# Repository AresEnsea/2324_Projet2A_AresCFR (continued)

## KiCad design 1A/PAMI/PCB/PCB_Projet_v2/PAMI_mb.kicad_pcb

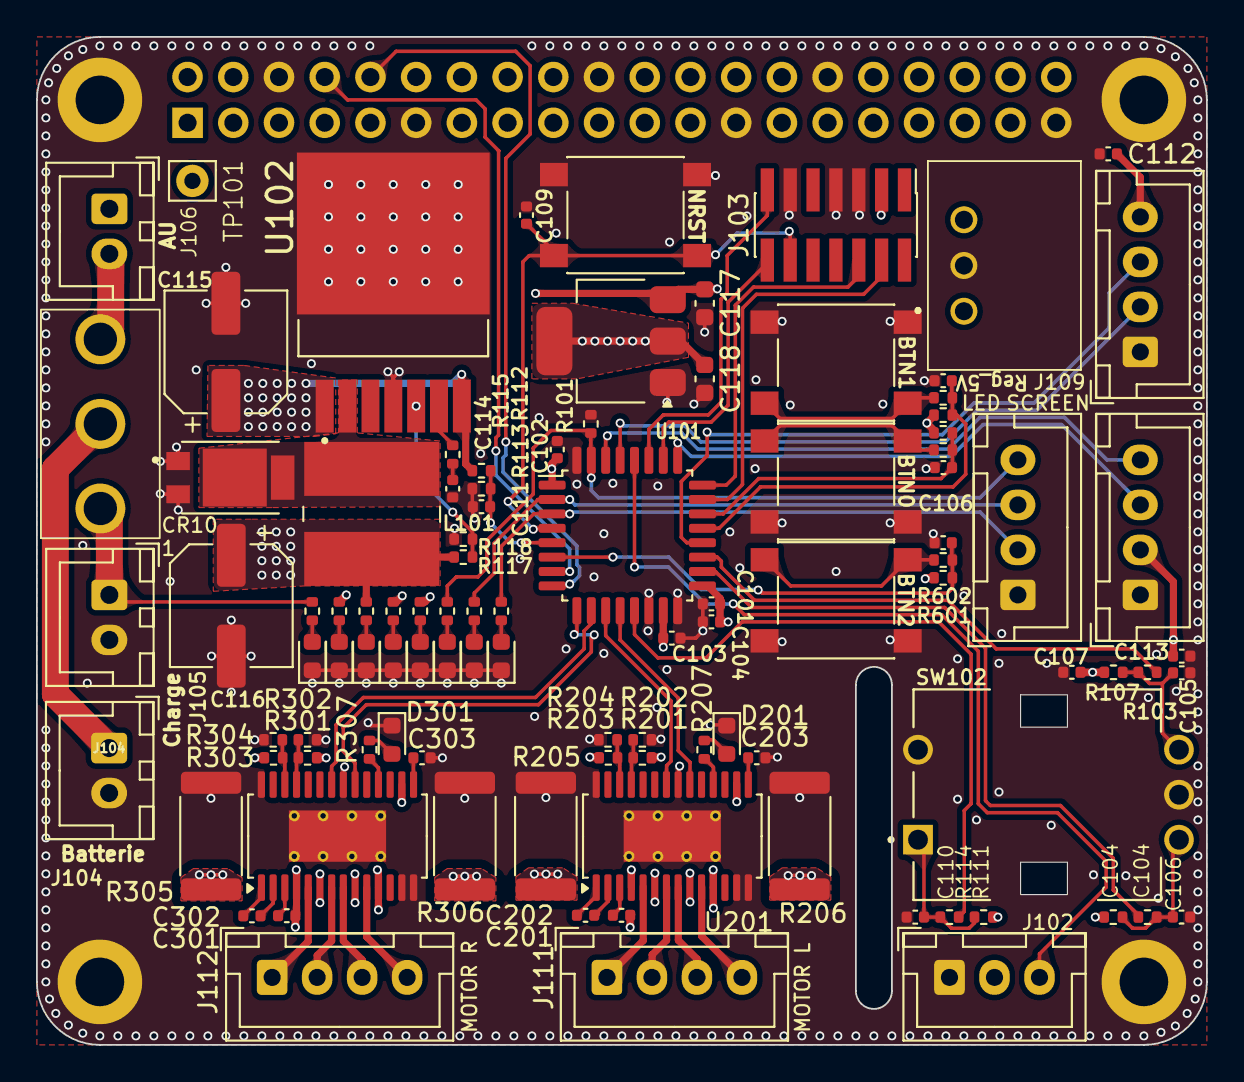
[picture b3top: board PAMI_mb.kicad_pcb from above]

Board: 4 copper layers, 65.0 x 56.0 mm, 106 parts (1 on the bottom side), 80 nets.

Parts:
C101, C102, C103, C107, C111, C201, C301: 100n; C_0402_1005Metric
C104: 10u; C_0402_1005Metric
C105, C106, C109, C110, C114, C401, C501, C601: 10n; C_0402_1005Metric
C112, C113: 1u; C_0402_1005Metric
C115: 100u; CP_Elec_6.3x7.7
C116: 47u; CP_Elec_6.3x5.4
C117, C118: 10u; C_0603_1608Metric
C202, C302: 22n; C_0402_1005Metric
C203, C303: 2u2; C_0402_1005Metric
CR101: DST10100S; DIO_MBR1045STR
D101, D105, D106, D107, D108: LED_RED; LED_0603_1608Metric
D102, D103, D104: LED_GREEN; LED_0603_1608Metric
D201, D301: LED; LED_0603_1608Metric
H101, H102, H103, H104: MountingHole_Pad; MountingHole_2.7mm_M2.5_DIN965_Pad
J101: Conn_02x20_Odd_Even; PinSocket_2x20_P2.54mm_Vertical
J102: Conn_01x03; JST_XH_B3B-XH-A_1x03_P2.50mm_Vertical
J103: Conn_ST_STDC14; PinHeader_2x07_P1.27mm_Vertical_SMD
J104: Battery; JST_XH_B2B-XH-A_1x02_P2.50mm_Vertical
J105: Charge; JST_XH_B2B-XH-A_1x02_P2.50mm_Vertical
J106: Stop; JST_XH_B2B-XH-A_1x02_P2.50mm_Vertical
J107, J109, J110, J111, J112: Conn_01x04; JST_XH_B4B-XH-A_1x04_P2.50mm_Vertical
J108: 173010542
L101: 220u; L_Wuerth_WE-PD2-Typ-L
R101: 100k; R_0402_1005Metric
R102: 560; R_0402_1005Metric
R103, R105, R107, R109, R111, R113, R114, R118, R401, R402, R501, R502, R601, R602: 10k; R_0402_1005Metric
R104, R106, R108, R120: 1k6; R_0402_1005Metric
R110: 5k6; R_0402_1005Metric
R112: 15k; R_0402_1005Metric
R115: 2.7k; R_0402_1005Metric
R116, R119: 3k6; R_0402_1005Metric
R117: 13k; R_0402_1005Metric
R201, R202, R203, R204, R301, R302, R303, R304: 0R; R_0402_1005Metric
R205, R206, R305, R306: 150m; R_2512_6332Metric
R207, R307: 1k; R_0402_1005Metric
SW101: SW_Push_SPDT; 472121010111
SW102: RotaryEncoder_Switch; SW_482016514001
SW103, SW401, SW501, SW601: SW_Push; SW_Push_1P1T_NO_6x6mm_H9.5mm
TP101: TestPoint; Pin_D0.9mm_L10.0mm_W2.4mm_FlatFork
U101: STM32G431KBTx; LQFP-32_7x7mm_P0.8mm
U102: LT1076CR-PBF; DPAK127P1394X457-8N
U103: AZ1117CH2-3.3TRG1; SOT-223-3_TabPin2
U201, U301: TMC2225-SA-T; HTSSOP-28-1EP_4.4x9.7mm_P0.65mm_EP2.85x5.4mm_ThermalVias

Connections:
+3.3V: C101.1, C102.1, C103.1, C104.1, C107.2, C113.1, C118.1, J102.2, J103.3 (VCC), J110.2, R107.2, R109.2, R111.1, R120.1, R201.2, R203.2, R301.2, R303.2, R401.1, R501.1, R601.1, U101.1 (VDD), U101.15 (VDDA), U101.17 (VDD), U103.2 (VO), U201.16 (VCC_IO), U301.16 (VCC_IO)
+5.1V: C116.1, J101.2, J101.4, L101.2, R117.1, R119.1
+5V: C112.1, C117.1, J108.3 (VOUT), J109.4, R116.1, U103.3 (VI)
/ADC_BATT: C111.1, R112.2, R113.1, U101.5 (PA0)
/DATA_RECEIVER: J102.3, U101.28 (PB5)
/DIR_MOTOR_L: U101.12 (PA7), U201.20 (DIR)
/DIR_MOTOR_R: U101.9 (PA4), U301.20 (DIR)
/ENCODEUR_A: R105.1, U101.18 (PA8)
/ENCODEUR_B: R103.1, U101.19 (PA9)
/ENCODEUR_BTN: R114.2, U101.13 (PB0)
/I2C_SCL: J110.3, U101.25 (PA15)
/I2C_SDA: J110.4, U101.30 (PB7)
/LIDAR_LP_RX: J109.3, U101.20 (PA10)
/LIDAR_LP_TX: J109.2, U101.29 (PB6)
/NRST: C109.1, J103.12 (~RST), SW103.1, U101.4 (PG10)
/PA1_USR_BTN_0: C401.1, R401.2, R402.1, U101.22 (PA12)
/PA11_USR_BTN_1: C501.1, R501.2, R502.1, U101.21 (PA11)
/PA12_USR_BTN_2: C601.1, R601.2, R602.1, U101.6 (PA1)
/PB8-BOOT0_LED0: J107.4, R101.1, R104.1, U101.31 (PB8)
/PF0_LED1: J107.3, R106.1, U101.2 (PF0)
/PF1_LED2: J107.2, R108.1, U101.3 (PF1)
/PWM_MOTOR_L_TIM2_CH1: U101.11 (PA6), U201.22 (STEP)
/PWM_MOTOR_R_TIM3_CH1: U101.10 (PA5), U301.22 (STEP)
/RASPBERRY_PI_RX: J101.10, U101.8 (PA3)
/RASPBERRY_PI_TX: J101.8, U101.7 (PA2)
/STLINK_RX: J103.13 (VCP_RX), U101.27 (PB4)
/STLINK_TX: J103.14 (VCP_TX), U101.26 (PB3)
/SWCLK: J103.6 (JCLK/SWCLK), U101.24 (PA14)
/SWDIO: J103.4 (JTMS/SWDIO), U101.23 (PA13)
/TMC2225/OA1: J111.2, U201.7 (OA1)
/TMC2225/OA2: J111.1, U201.5 (OA2)
/TMC2225/OB1: J111.3, U201.8 (OB1)
/TMC2225/OB2: J111.4, U201.10 (OB2)
/TMC2226/OA1: J112.2, U301.7 (OA1)
/TMC2226/OA2: J112.1, U301.5 (OA2)
/TMC2226/OB1: J112.3, U301.8 (OB1)
/TMC2226/OB2: J112.4, U301.10 (OB2)
/VFB: R117.2, R118.1, U102.5 (FB)
/V_BAT: J104.1, SW101.2 (B)
/V_CHARGE: J105.1, R102.1, SW101.3 (C)
/Vsw: CR101.3, L101.1, U102.2 (Vsw)
GND: C101.2, C102.2, C103.2, C104.2, C105.2, C106.2, C107.1, C109.2, C110.2, C111.2, C112.2, C113.2, C114.2, C115.2, C116.2, C117.2, C118.2, C203.1, C303.1, C401.2, C501.2, C601.2, CR101.1, CR101.2, D101.1 (K), D102.1 (K), D103.1 (K), D104.1 (K), D105.1 (K), D106.1 (K), D107.1 (K), D108.1 (K), D201.1 (K), D301.1 (K), H101.1, H102.1, H103.1, H104.1, J101.6, J101.11, J101.20, J101.25, J101.30, J101.39, J102.1, J103.5 (GND), J103.7 (GND), J103.11 (GNDDetect), J104.2, J105.2, J107.1, J108.2 (GND), J109.1, J110.1, R101.2, R113.2, R118.2, R202.1, R204.1, R205.2, R206.2, R302.1, R304.1, R305.2, R306.2, SW102.C, SW102.S2, SW103.2, SW401.2, SW501.2, SW601.2, U101.14 (VSSA), U101.16 (VSS), U101.32 (VSS), U102.4 (GND), U103.1 (GND), U201.13 (TEST), U201.14 (GND), U201.21 (ENN), U201.28 (GND), U201.29 (PAD), U301.13 (TEST), U301.14 (GND), U301.21 (ENN), U301.28 (GND), U301.29 (PAD)
unnamed: C105.1, R103.2, R107.1, SW102.B
unnamed: C106.1, R105.2, R109.1, SW102.A
unnamed: C110.1, R111.2, R114.1, SW102.S1
unnamed: C114.1, R115.2
unnamed: D101.2 (A), R102.2
unnamed: D102.2 (A), R104.2
unnamed: D103.2 (A), R106.2
unnamed: D104.2 (A), R108.2
unnamed: D105.2 (A), R110.2
unnamed: D106.2 (A), R116.2
unnamed: D107.2 (A), R119.2
unnamed: D108.2 (A), R120.2
unnamed: D201.2 (A), R207.1
unnamed: D301.2 (A), R307.1
unnamed: J106.2, SW101.1 (A)
unnamed: R402.2, SW401.1
unnamed: R502.2, SW501.1
unnamed: R602.2, SW601.1
unnamed: R115.1, U102.6 (Vc)
unnamed: C203.2, U201.15 (5VOUT)
unnamed: R205.1, U201.6 (BRA)
unnamed: R206.1, U201.9 (BRB)
unnamed: C202.1, U201.2 (CPI)
unnamed: C202.2, U201.1 (CPO)
unnamed: R207.2, U201.18 (DIAG)
unnamed: R201.1, R202.2, U201.25 (MS1)
unnamed: R203.1, R204.2, U201.26 (MS2)
unnamed: C201.2, U201.3 (VCP)
unnamed: C303.2, U301.15 (5VOUT)
unnamed: R305.1, U301.6 (BRA)
unnamed: R306.1, U301.9 (BRB)
unnamed: C302.1, U301.2 (CPI)
unnamed: C302.2, U301.1 (CPO)
unnamed: R307.2, U301.18 (DIAG)
unnamed: R301.1, R302.2, U301.25 (MS1)
unnamed: R303.1, R304.2, U301.26 (MS2)
unnamed: C301.2, U301.3 (VCP)
VCC: C115.1, C201.1, C301.1, J106.1, J108.1 (VIN), R110.1, R112.1, TP101.1, U102.1 (Vin), U102.7 (Shutdown), U201.4 (VS), U201.11 (VS), U301.4 (VS), U301.11 (VS)

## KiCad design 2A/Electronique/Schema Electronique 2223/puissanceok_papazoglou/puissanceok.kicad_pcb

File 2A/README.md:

# 2A
Ce dossier regroupe les fichiers réalisés par les étudiants en deuxième année de l'association

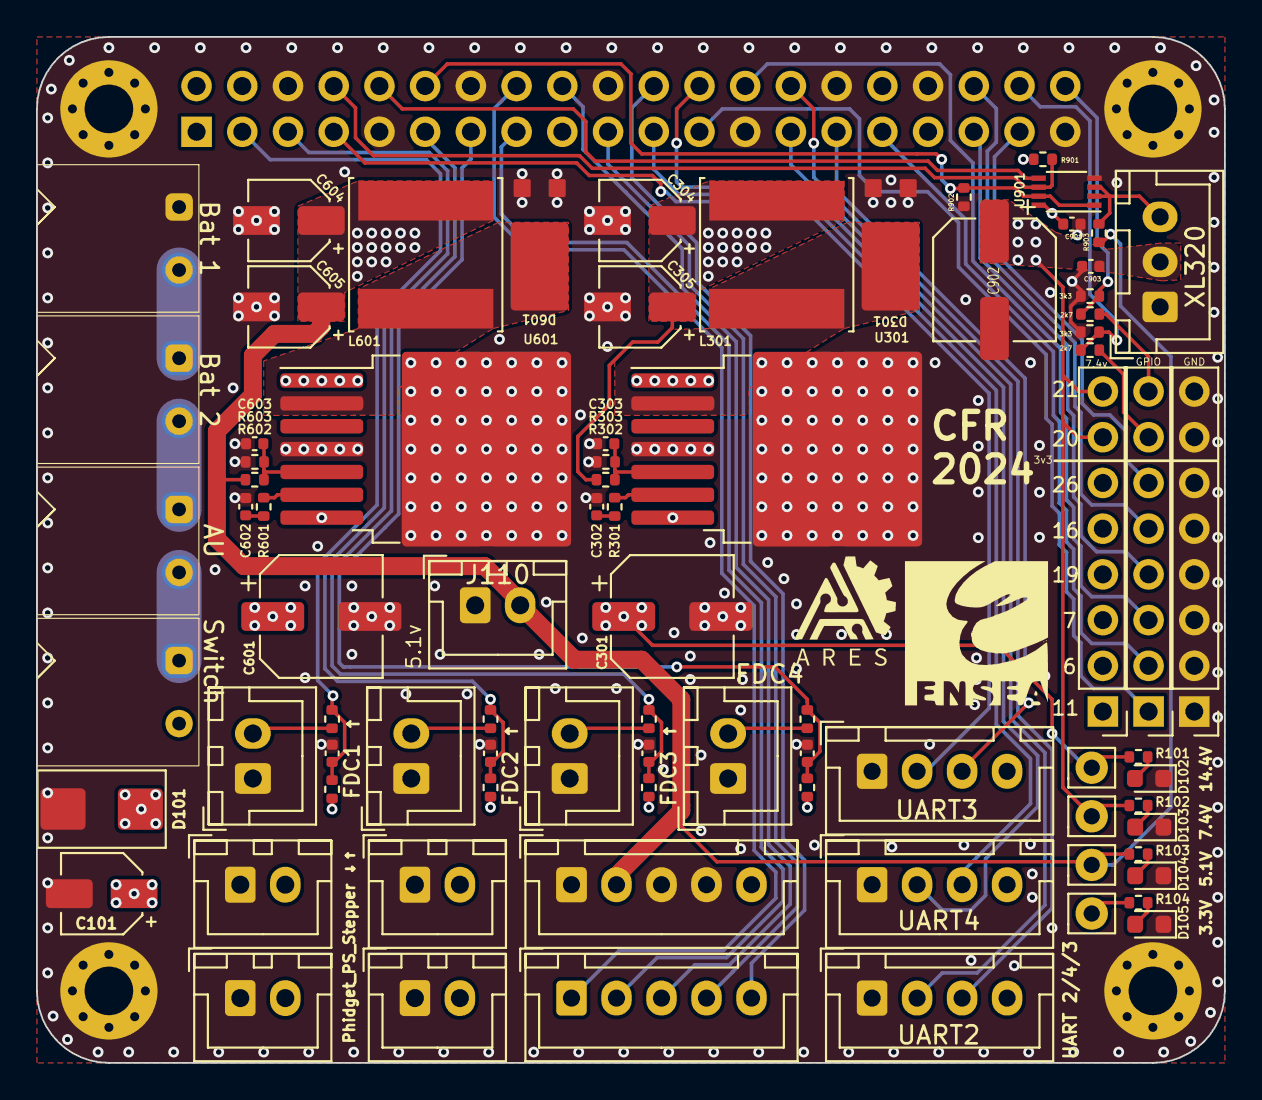
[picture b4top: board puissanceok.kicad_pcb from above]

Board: 4 copper layers, 66.0 x 57.0 mm, 86 parts (1 on the bottom side), 53 nets.

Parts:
C101: 10u; CP_Elec_4x5.4
C201, C401, C501, C701, C901, C903: 100n; C_0402_1005Metric
C301, C601, C902: 100u; CP_Elec_6.3x7.7
C302, C303, C602, C603: 10n; C_0402_1005Metric
C304, C305, C604, C605: 22u; CP_Elec_4x5.4
D101: TVS 20.5V; D_SMB
D102, D103, D104, D105: LED; LED_0603_1608Metric
D301, D601: D_Schottky; DST10100S
H101, H102, H103, H104: MountingHole_Pad; MountingHole_2.7mm_M2.5_Pad_Via
J101: Bat 2; 691322110002
J102: Bat 1; 691322110002
J103: AU; 691322110002
J104: Switch; 691322110002
J105: Conn_RPI; PinSocket_2x20_P2.54mm_Vertical
J106: Conn_Phidget_PS_Stepper_1; JST_XH_B2B-XH-A_1x02_P2.50mm_Vertical
J107: Conn_Phidget_PS_Stepper_2; JST_XH_B2B-XH-A_1x02_P2.50mm_Vertical
J108: Conn_Phidget_PS_Stepper_3; JST_XH_B2B-XH-A_1x02_P2.50mm_Vertical
J109: Conn_Phidget_PS_Stepper_4; JST_XH_B2B-XH-A_1x02_P2.50mm_Vertical
J110: Conn_01x02; JST_XH_B2B-XH-A_1x02_P2.50mm_Vertical
J111: Conn_GND; PinHeader_1x08_P2.54mm_Vertical
J112: Conn_GPIO_unused; PinHeader_1x08_P2.54mm_Vertical
J113: Conn_3.3V; PinHeader_1x08_P2.54mm_Vertical
J114, J115: Conn_01x05; JST_XH_B5B-XH-A_1x05_P2.50mm_Vertical
J201, J401, J501, J701: Conn_FDC; JST_XH_B2B-XH-A_1x02_P2.50mm_Vertical
J801, J1001, J1101: Conn_UART; JST_XH_B4B-XH-A_1x04_P2.50mm_Vertical
J901: Conn_XL320; JST_XH_B3B-XH-A_1x03_P2.50mm_Vertical
L301, L601: 22m; L_Changjiang_FNR8065S
R1, R3: 2k7; R_0402_1005Metric
R2, R4: 3k3; R_0402_1005Metric
R101: 4k7; R_0402_1005Metric
R102: 1k8; R_0402_1005Metric
R103, R104, R202, R402, R502, R702: 1k; R_0402_1005Metric
R201, R401, R501, R701: 100k; R_0402_1005Metric
R301, R601: 2.7k; R_0402_1005Metric
R302, R602: 2k87; R_0402_1005Metric
R303, R603: 2k2; R_0402_1005Metric
R901, R902, R903: 10k; R_0402_1005Metric
TP101: TestPoint; Pin_D0.9mm_L10.0mm_W2.4mm_FlatFork
TP102: 5.1V; Pin_D0.9mm_L10.0mm_W2.4mm_FlatFork
TP103: 7.4V; Pin_D0.9mm_L10.0mm_W2.4mm_FlatFork
TP104: 3V3; Pin_D0.9mm_L10.0mm_W2.4mm_FlatFork
U301, U601: LT1076CR-PBF; TO-263-7_TabPin4
U901: 74LVC2G241; VSSOP-8_2.3x2mm_P0.5mm

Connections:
5.1V: C604.1, C605.1, J105.2, J105.4, J110.2, J114.2, L601.2, R103.1, R602.1, R903.1, TP102.1
7.4V: C304.1, C305.1, C902.1, C903.1, J113.7, J113.8, J901.2, L301.2, R102.1, R302.1, TP103.1
14.4V: C101.1, C301.1, C601.1, D101.1 (A1), J104.2, J106.2, J107.2, J108.2, J109.2, R101.1, TP101.1, U301.1 (Vin), U301.7 (Shutdown), U601.1 (Vin), U601.7 (Shutdown)
+3.3V: C901.1, J105.17, J113.1, J113.2, J113.3, J113.4, J113.5, J113.6, J114.5, J801.4, J1001.4, J1101.4, R104.1, R201.1, R401.1, R501.1, R701.1, R901.1, TP104.1, U901.8 (VCC)
/BUCK_5.1V/vc: R601.1, U601.6 (Vc)
/BUCK_5.1V/voutbuck: D601.1 (K), L601.1, U601.2 (Vsw)
/BUCK_7.4V/vc: R301.1, U301.6 (Vc)
/BUCK_7.4V/voutbuck: D301.1 (K), L301.1, U301.2 (Vsw)
/FDC_1: C201.1, J105.3, R201.2, R202.1
/FDC_2: C401.1, J105.5, R401.2, R402.1
/FDC_3: C501.1, J105.11, R501.2, R502.1
/FDC_4: C701.1, J105.13, R701.2, R702.1
/GPIO6: J105.31, J112.2
/GPIO7: J105.26, J112.3
/GPIO11: J105.23, J112.1
/GPIO16: J105.36, J112.5
/GPIO19: J105.35, J112.4
/GPIO20: J105.38, R3.2, R4.1
/GPIO21: J105.40, R1.2, R2.1
/GPIO26: J105.37, J112.6
/Out_color_sensor: J105.16, J115.1
/S0_color_sensor: J105.22, J115.5
/S1_color_sensor: J105.19, J115.4
/S2_color_sensor: J105.18, J115.3
/S3_color_sensor: J105.15, J115.2
/Uart1_RX: J105.10, U901.5
/Uart1_TX: J105.8, R901.2, U901.6
/Uart2_RX: J105.28, J801.3
/Uart2_TX: J105.27, J801.2
/Uart3_RX: J105.29, J1001.3
/Uart3_TX: J105.7, J1001.2
/Uart4_RX: J105.21, J1101.3
/Uart4_TX: J105.24, J1101.2
/UartTX_Enable: J105.12, R902.1, U901.1, U901.7
/V_BAT: J101.2, J103.1
/XL_320_connector_and_buffer/DXL_Data: J901.3, R903.2, U901.2, U901.3
GND: C101.2, C201.2, C301.2, C302.2, C303.2, C304.2, C305.2, C401.2, C501.2, C601.2, C602.2, C603.2, C604.2, C605.2, C701.2, C901.2, C902.2, C903.2, D101.2 (A2), D102.1 (K), D103.1 (K), D104.1 (K), D105.1 (K), D301.2 (A), D601.2 (A), H101.1, H102.1, H103.1, H104.1, J102.1, J105.6, J105.9, J105.14, J105.20, J105.25, J105.30, J105.34, J105.39, J106.1, J107.1, J108.1, J109.1, J110.1, J111.1, J111.2, J111.3, J111.4, J111.5, J111.6, J111.7, J111.8, J114.1, J114.3, J114.4, J201.1, J401.1, J501.1, J701.1, J801.1, J901.1, J1001.1, J1101.1, R2.2, R4.2, R303.2, R603.2, R902.2, U301.4 (GND), U601.4 (GND), U901.4 (GND)
unnamed: C302.1, R301.2
unnamed: C602.1, R601.2
unnamed: D102.2 (A), R101.2
unnamed: D103.2 (A), R102.2
unnamed: D104.2 (A), R103.2
unnamed: D105.2 (A), R104.2
unnamed: J101.1, J102.2
unnamed: J103.2, J104.1
unnamed: J112.7, R3.1
unnamed: J112.8, R1.1
unnamed: J201.2, R202.2
unnamed: J401.2, R402.2
unnamed: J501.2, R502.2
unnamed: J701.2, R702.2
unnamed: C303.1, R302.2, R303.1, U301.5 (FB)
unnamed: C603.1, R602.2, R603.1, U601.5 (FB)

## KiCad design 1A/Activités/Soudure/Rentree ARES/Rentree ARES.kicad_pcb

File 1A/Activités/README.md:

# Activités
Ce dossier regroupe deux livrets rédigés par Ousmane THIONGANE. L'un permet de découvrir la programmation avec Mbed, et l'autre le routage avec KiCad. Il peuvent être réutilisés au fil des années pour réaliser des activités de rentrée, ou simplement pour s'exercer à l'électronique et l'informatique.

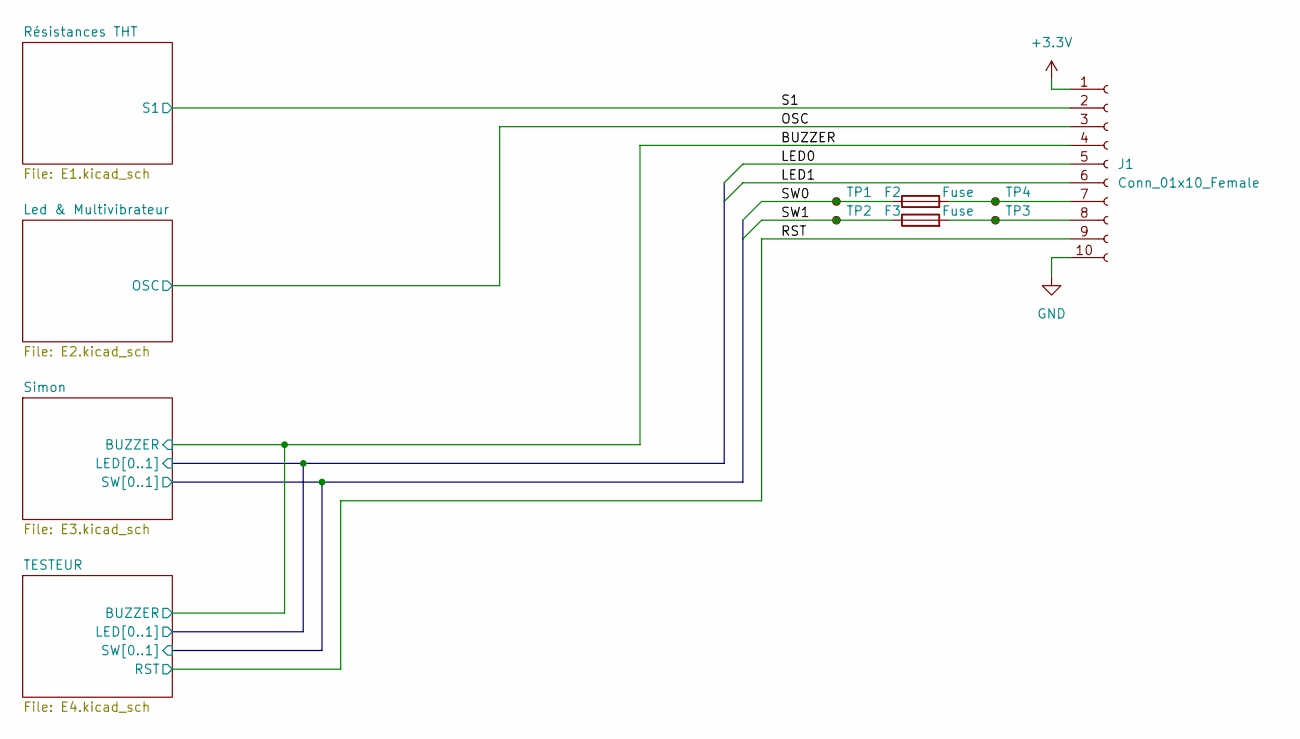
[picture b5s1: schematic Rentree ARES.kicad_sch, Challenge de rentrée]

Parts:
F2, F3: Fuse; Fuse_internal_trace
J1: Conn_01x10_Female; PinHeader_1x10_P2.54mm_Horizontal
TP1, TP2, TP3, TP4: TestPoint_Small; TestPoint_Pad_D1.5mm

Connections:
+3.3V: J1.1; also elsewhere on the board
/BUZZER: J1.4; also elsewhere on the board
/OSC: J1.3; also elsewhere on the board
/RST: J1.9; also elsewhere on the board
/S1: J1.2; also elsewhere on the board
/Simon un peu plus dur/LED0: J1.5; also elsewhere on the board
/Simon un peu plus dur/LED1: J1.6; also elsewhere on the board
/Simon un peu plus dur/SW0: F2.1, TP1.1; also elsewhere on the board
/Simon un peu plus dur/SW1: F3.1, TP2.1; also elsewhere on the board
GND: J1.10; also elsewhere on the board
unnamed: F2.2, J1.7, TP4.1
unnamed: F3.2, J1.8, TP3.1

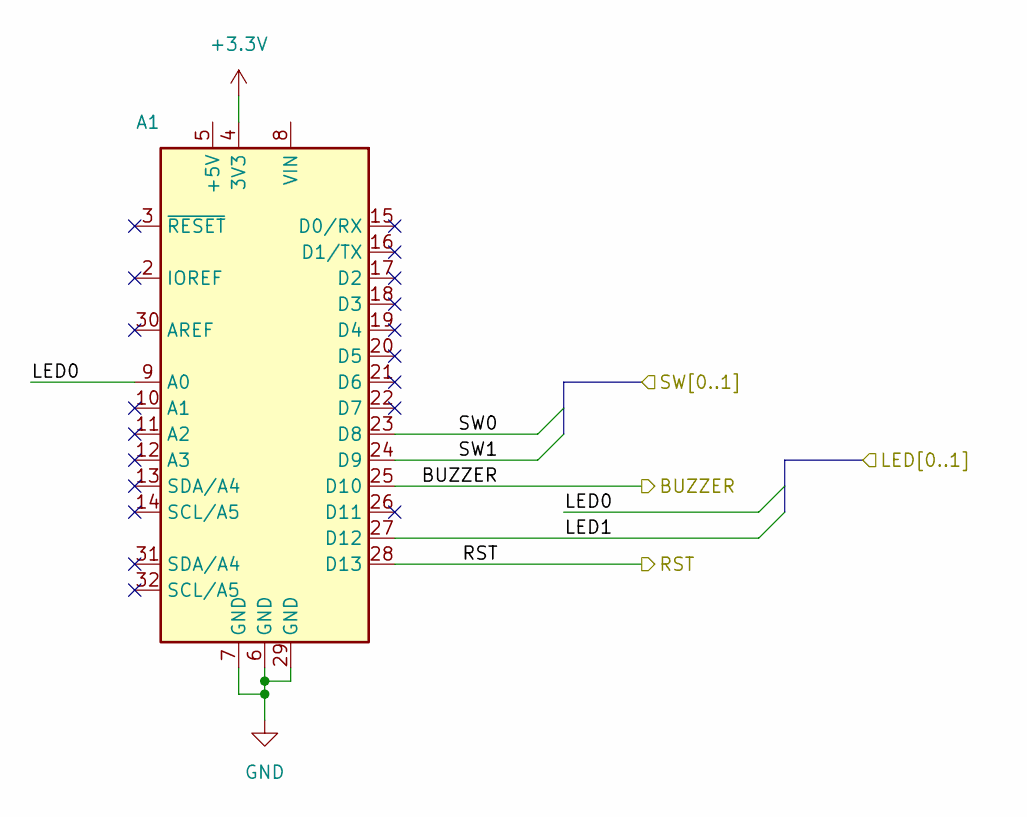
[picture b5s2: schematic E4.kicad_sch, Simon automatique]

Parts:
A1: Arduino_UNO_R3

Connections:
+3.3V: A1.4 (3V3); also elsewhere on the board
/BUZZER: A1.25 (D10); also elsewhere on the board
/RST: A1.28 (D13); also elsewhere on the board
/Simon un peu plus dur/LED0: A1.9 (A0); also elsewhere on the board
/Simon un peu plus dur/LED1: A1.27 (D12); also elsewhere on the board
/Simon un peu plus dur/SW0: A1.23 (D8); also elsewhere on the board
/Simon un peu plus dur/SW1: A1.24 (D9); also elsewhere on the board
GND: A1.6 (GND), A1.7 (GND), A1.29 (GND); also elsewhere on the board

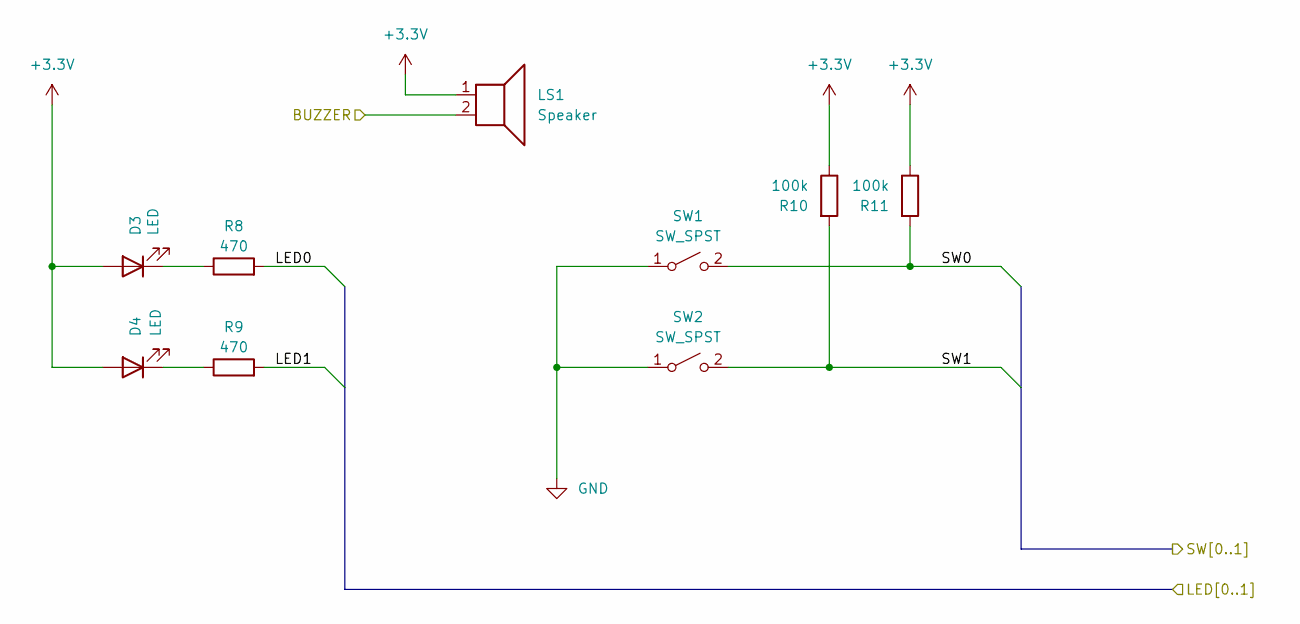
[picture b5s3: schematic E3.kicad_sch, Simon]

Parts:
D3, D4: LED; LED_D5.0mm_Clear
LS1: Speaker; MagneticBuzzer_ProSignal_ABT-410-RC
R8, R9: 470; R_0805_2012Metric
R10, R11: 100k; R_0805_2012Metric
SW1, SW2: SW_SPST; SW_PUSH_6mm_H5mm

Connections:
+3.3V: D3.2 (A), D4.2 (A), LS1.1, R10.1, R11.1; also elsewhere on the board
/BUZZER: LS1.2; also elsewhere on the board
/Simon un peu plus dur/LED0: R8.2; also elsewhere on the board
/Simon un peu plus dur/LED1: R9.2; also elsewhere on the board
/Simon un peu plus dur/SW0: R11.2, SW1.2 (B); also elsewhere on the board
/Simon un peu plus dur/SW1: R10.2, SW2.2 (B); also elsewhere on the board
GND: SW1.1 (A), SW2.1 (A); also elsewhere on the board
unnamed: D3.1 (K), R8.1
unnamed: D4.1 (K), R9.1

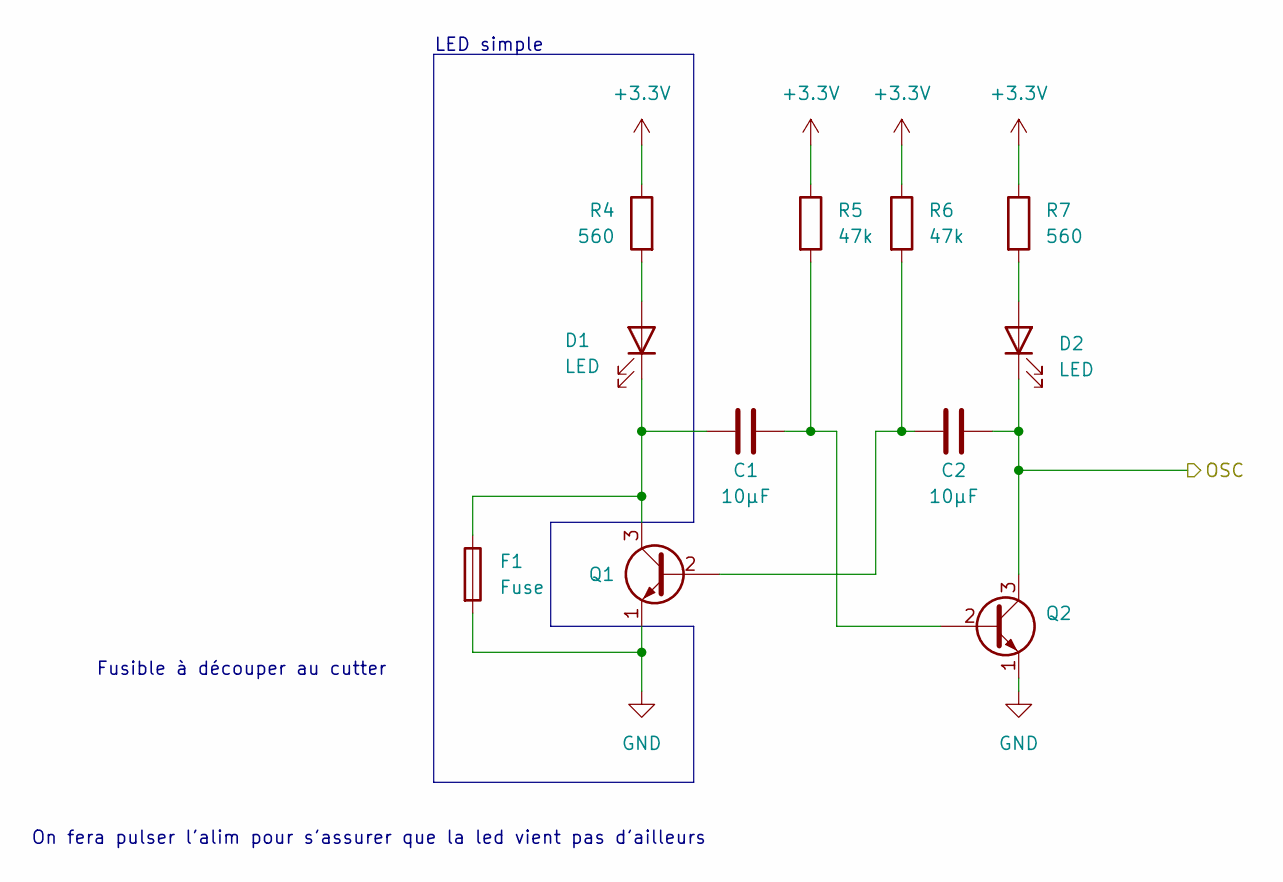
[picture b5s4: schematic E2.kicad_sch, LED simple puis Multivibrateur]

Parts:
C1, C2: 10µF; C_1206_3216Metric
D1, D2: LED; LED_D5.0mm_Clear
F1: Fuse; Fuse_trace
Q1, Q2: Q_NPN_EBC; TO-92_Inline
R4, R7: 560; R_0805_2012Metric
R5, R6: 47k; R_0805_2012Metric

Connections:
+3.3V: R4.1, R5.1, R6.1, R7.1; also elsewhere on the board
/OSC: C2.1, D2.1 (K), Q2.3 (C); also elsewhere on the board
GND: F1.2, Q1.1 (E), Q2.1 (E); also elsewhere on the board
unnamed: C1.1, Q2.2 (B), R5.2
unnamed: C1.2, D1.1 (K), F1.1, Q1.3 (C)
unnamed: C2.2, Q1.2 (B), R6.2
unnamed: D1.2 (A), R4.2
unnamed: D2.2 (A), R7.2

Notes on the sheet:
LED simple
Fusible à découper au cutter
On fera pulser l'alim pour s'assurer que la led vient pas d'ailleurs

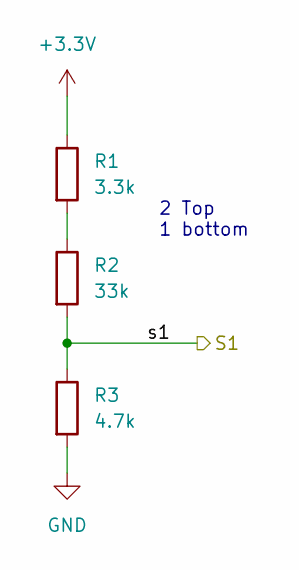
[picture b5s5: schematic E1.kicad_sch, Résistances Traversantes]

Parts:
R1: 3.3k; R_Axial_DIN0207_L6.3mm_D2.5mm_P2.54mm_Vertical
R2: 33k; R_Axial_DIN0207_L6.3mm_D2.5mm_P10.16mm_Horizontal
R3: 4.7k; R_Axial_DIN0207_L6.3mm_D2.5mm_P10.16mm_Horizontal

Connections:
+3.3V: R1.1; also elsewhere on the board
/S1: R2.2, R3.1; also elsewhere on the board
GND: R3.2; also elsewhere on the board
unnamed: R1.2, R2.1

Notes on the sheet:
2 Top 1 bottom

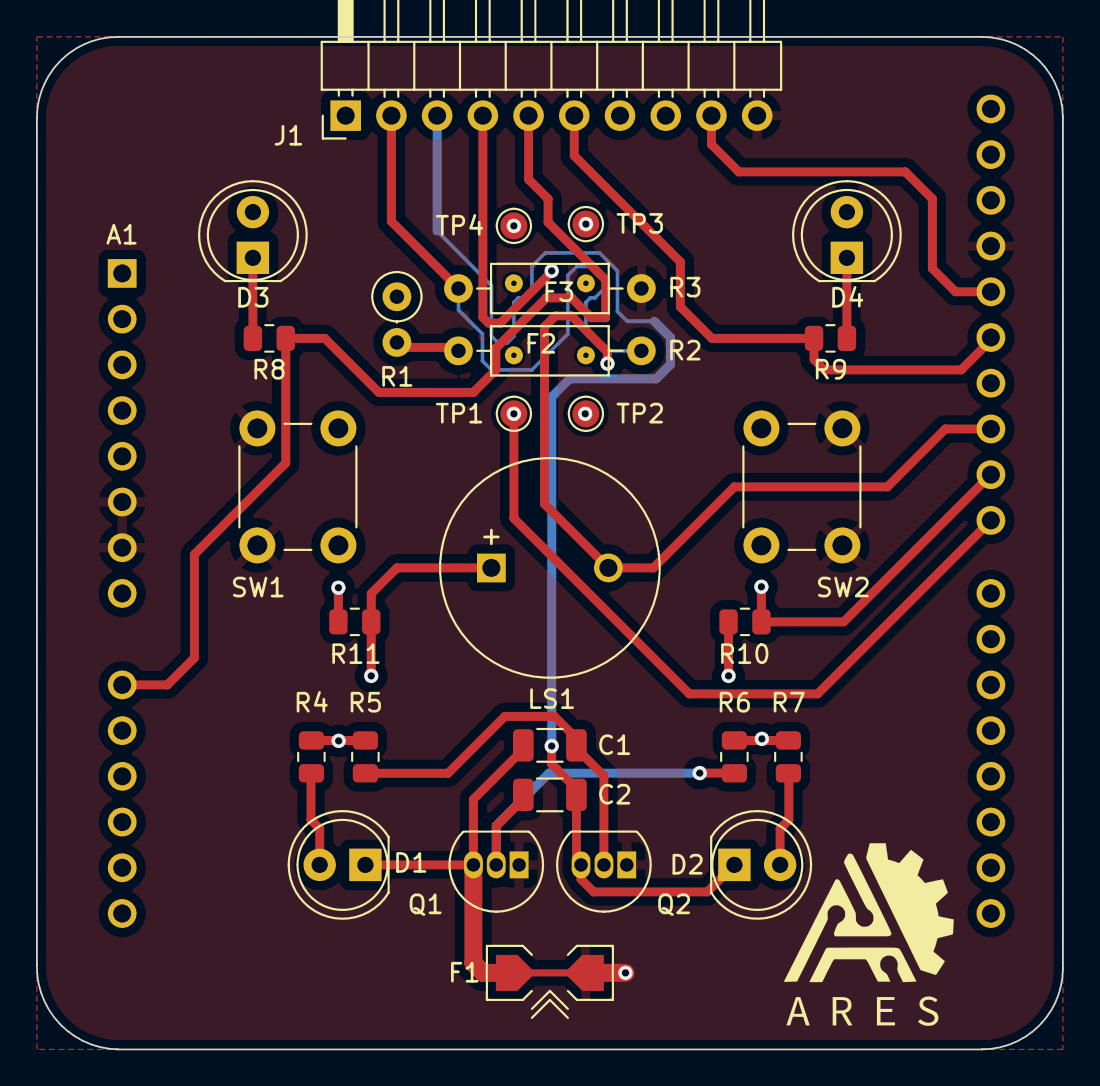
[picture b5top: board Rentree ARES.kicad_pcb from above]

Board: 4 copper layers, 57.0 x 56.2 mm, 31 parts (0 on the bottom side), 20 nets.

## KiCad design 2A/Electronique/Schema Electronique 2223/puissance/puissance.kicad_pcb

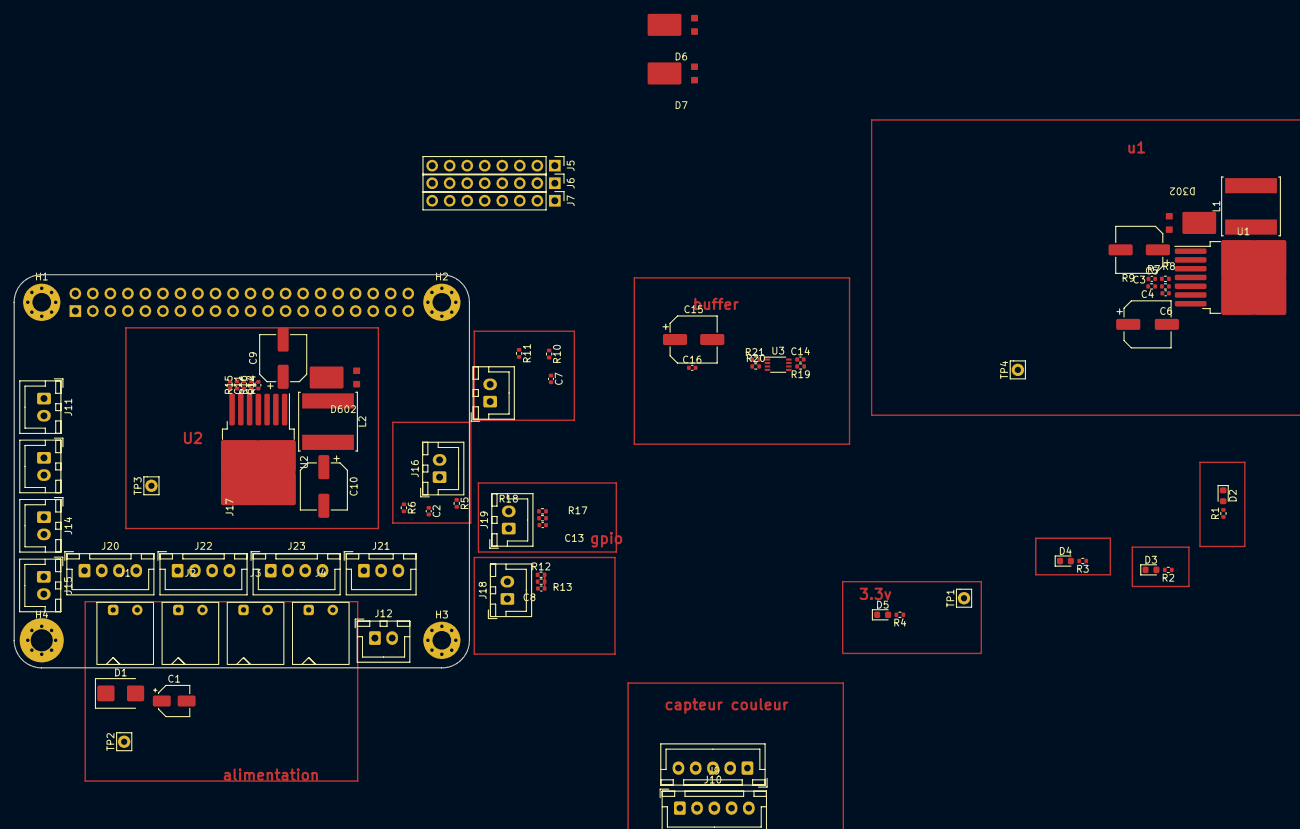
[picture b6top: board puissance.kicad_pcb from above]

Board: 2 copper layers, 82 parts (1 on the bottom side), 34 nets.

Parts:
C1: 10u; CP_Elec_4x5.4
C2, C5, C14, C16: 100n; C_0402_1005Metric
C3: 100n; CP_Elec_6.3x7.7
C4: 100n; CP_Elec_6.3x5.4
C6: 100u; C_0402_1005Metric
C7, C8, C11, C12: 10n; C_0402_1005Metric
C9: 47u; CP_Elec_6.3x7.7
C10: 100u; CP_Elec_6.3x5.4
C13: 47u; C_0402_1005Metric
C15: 100u; CP_Elec_6.3x7.7
D1: TVS 20.5V; D_SMB
D2, D3, D4, D5: LED; LED_0603_1608Metric
D6, D7, D302, D602: D_Schottky; DST10100S
H1, H2, H3, H4: MountingHole_Pad; MountingHole_2.7mm_M2.5_Pad_Via
J1: Bat 2; 691322110002
J2: Bat 1; 691322110002
J3: AU; 691322110002
J4: Switch; 691322110002
J5: Conn_RPI; PinHeader_1x08_P2.54mm_Vertical
J6: Conn_Phidget_PS_Stepper_1; PinHeader_1x08_P2.54mm_Vertical
J7: Conn_Phidget_PS_Stepper_2; PinHeader_1x08_P2.54mm_Vertical
J8: Conn_Phidget_PS_Stepper_3; PinSocket_2x20_P2.54mm_Vertical
J9: Conn_Phidget_PS_Stepper_4; JST_XH_B5B-XH-A_1x05_P2.50mm_Vertical
J10: Conn_01x02; JST_XH_B5B-XH-A_1x05_P2.50mm_Vertical
J11: Conn_GND; JST_XH_B2B-XH-A_1x02_P2.50mm_Vertical
J12: Conn_GPIO_unused; JST_XH_B2B-XH-A_1x02_P2.50mm_Vertical
J13: Conn_3.3V; JST_XH_B2B-XH-A_1x02_P2.50mm_Vertical
J14, J15: Conn_01x05; JST_XH_B2B-XH-A_1x02_P2.50mm_Vertical
J16, J17, J18, J19: Conn_FDC; JST_XH_B2B-XH-A_1x02_P2.50mm_Vertical
J20, J23: Conn_UART; JST_XH_B4B-XH-A_1x04_P2.50mm_Vertical
J21: Conn_UART; JST_XH_B3B-XH-A_1x03_P2.50mm_Vertical
J22: Conn_XL320; JST_XH_B4B-XH-A_1x04_P2.50mm_Vertical
L1, L2: 22m; L_Changjiang_FNR8065S
R1: 4k7; R_0402_1005Metric
R2: 1k8; R_0402_1005Metric
R3, R4, R6, R8, R10, R12: 1k; R_0402_1005Metric
R5, R7, R9, R11: 100k; R_0402_1005Metric
R13, R16: 2.7k; R_0402_1005Metric
R14, R17: 2k87; R_0402_1005Metric
R15, R18: 2k2; R_0402_1005Metric
R19, R20, R21: 10k; R_0402_1005Metric
TP1: TestPoint; Pin_D0.9mm_L10.0mm_W2.4mm_FlatFork
TP2: 5.1V; Pin_D0.9mm_L10.0mm_W2.4mm_FlatFork
TP3: 7.4V; Pin_D0.9mm_L10.0mm_W2.4mm_FlatFork
TP4: 3V3; Pin_D0.9mm_L10.0mm_W2.4mm_FlatFork
U1, U2: LT1076CR-PBF; TO-263-7_TabPin4
U3: 74LVC2G241; VSSOP-8_2.3x2mm_P0.5mm

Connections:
5.1V: C13.1, J5.2, J5.4, J10.2, L2.2, R3.1, R17.1, R21.1, TP2.1
7.4V: C9.1, C15.1, C16.1, J22.2, L1.2, R2.1, R14.1, TP3.1
+3.3V: C14.1, J5.1, J13.1, J13.2, J20.4, J23.4, R4.1, R5.1, R7.1, R9.1, R11.1, R19.1, TP4.1, U3.8 (VCC)
/FDC_1: C4.1, R9.2, R10.1
/FDC_2: C3.1, R7.2, R8.1
/FDC_3: C5.1, R11.2, R12.1
/FDC_4: C2.1, R5.2, R6.1
/GPIO2: J5.3, J12.1
/GPIO3: J5.5, J12.2
/Uart1_TX: J5.8, R19.2, U3.6
/Uart3_TX: J5.7, J21.2
/UartTX_Enable: R20.1, U3.1, U3.7
/V_BAT: J1.2, J3.1
/XL_320_connector_and_buffer/DXL_Data: J22.3, R21.2, U3.2, U3.3
GND: C1.2, C2.2, C3.2, C4.2, C5.2, C6.2, C7.2, C8.2, C9.2, C10.2, C11.2, C12.2, C13.2, C14.2, C15.2, C16.2, D1.2 (A2), D2.1 (K), D3.1 (K), D4.1 (K), D5.1 (K), D6.2 (A), D7.2 (A), H1.1, H2.1, H3.1, H4.1, J2.1, J5.6, J6.1, J7.1, J8.1, J9.1, J10.1, J11.1, J11.2, J14.2, J16.1, J17.1, J18.1, J19.1, J20.1, J21.1, J22.1, J23.1, R15.2, R18.2, R20.2, U1.4 (GND), U2.4 (GND), U3.4 (GND)
unnamed: C7.1, R13.2
unnamed: C11.1, R16.2
unnamed: D2.2 (A), R1.2
unnamed: D3.2 (A), R2.2
unnamed: D4.2 (A), R3.2
unnamed: D5.2 (A), R4.2
unnamed: D6.1 (K), L1.1, U1.2 (Vsw)
unnamed: D7.1 (K), L2.1, U2.2 (Vsw)
unnamed: J1.1, J2.2
unnamed: J3.2, J4.1
unnamed: J16.2, R6.2
unnamed: J17.2, R8.2
unnamed: J18.2, R10.2
unnamed: J19.2, R12.2
unnamed: C8.1, R14.2, R15.1, U1.5 (FB)
unnamed: R13.1, U1.6 (Vc)
unnamed: C12.1, R17.2, R18.1, U2.5 (FB)
unnamed: R16.1, U2.6 (Vc)
Vin: C1.1, C6.1, C10.1, D1.1 (A1), J4.2, J6.2, J7.2, J8.2, J9.2, TP1.1, U1.1 (Vin), U1.7 (Shutdown), U2.1 (Vin), U2.7 (Shutdown)

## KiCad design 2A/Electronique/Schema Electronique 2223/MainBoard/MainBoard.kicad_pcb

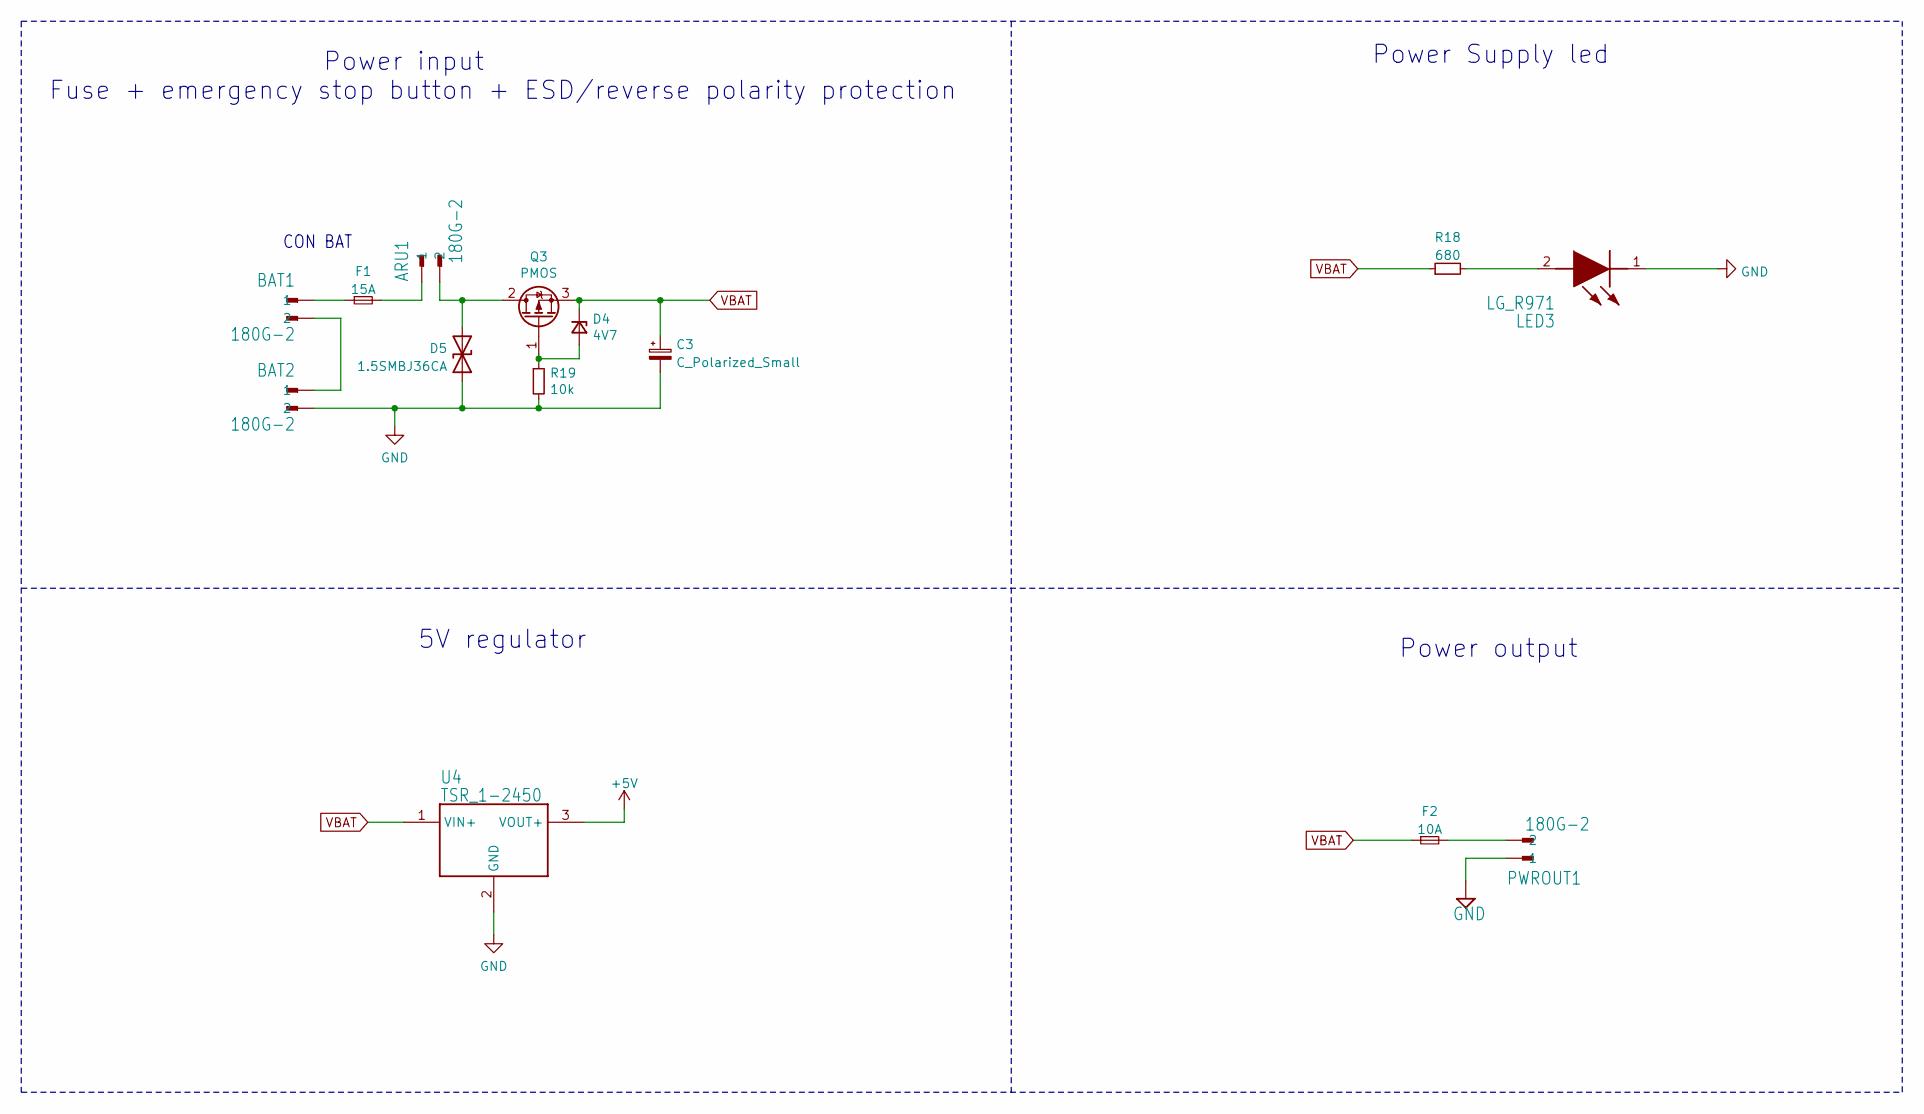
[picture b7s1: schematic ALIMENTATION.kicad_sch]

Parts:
ARU1: 180G-2
BAT1, BAT2: 180G-2
C3: C_Polarized_Small; E5-6
D4: 4V7; D_0603_1608Metric; Mouser Part Number 771-BZX84J-C4V7115
D5: 1.5SMBJ36CA; D_SMB; Mouser Part Number 652-1.5SMBJ36CA-H
F1: 15A; Fuse_1206_3216Metric_Pad1.42x1.75mm_HandSolder; Mouser Part Number 693-3413.0330.22
F2: 10A; Fuse_1206_3216Metric_Pad1.42x1.75mm_HandSolder; Mouser Part Number 530-0685P9100-01
LED3: LG_R971; LEDC2012X90N
PWROUT1: 180G-2
Q3: PMOS; MOS_WDFN8; Mouser Part Number 863-NTTFS015P03P8ZWG
R18: 680; R_0805_2012Metric_Pad1.20x1.40mm_HandSolder
R19: 10k; R_0805_2012Metric_Pad1.20x1.40mm_HandSolder
U4: TSR_1-2450; TSR-1-24120

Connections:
+5V: U4.3 (VOUT+); also elsewhere on the board
GND: BAT2.2, C3.2, C3.-, D5.1 (A1), LED3.1 (K), PWROUT1.1, R19.2, U4.2 (GND); also elsewhere on the board
unnamed: ARU1.1, F1.2
unnamed: BAT1.1, F1.1
unnamed: BAT1.2, BAT2.1
unnamed: D4.2 (A), Q3.1 (G), R19.1
unnamed: ARU1.2, D5.2 (A2), Q3.2 (D)
unnamed: F2.2, PWROUT1.2
unnamed 37: LED3.2 (A), R18.2; also elsewhere on the board
VBAT: C3.1, C3.+, D4.1 (K), F2.1, Q3.3 (S), R18.1, U4.1 (VIN+); also elsewhere on the board

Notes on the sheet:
Power Supply led
Power output
CON BAT
Power input Fuse + emergency stop button + ESD/reverse polarity protection
5V regulator
